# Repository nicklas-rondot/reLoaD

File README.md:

# *reLoaD* framework

The *reLoaD* (reconfigurable Lab on a Disc) framework is an open-hardware centrifugal microfluidics framework for research, teaching and application. It consists of three core modules:

1. The *Motor* module:
  Consists of a consumer-grade brushless DC (BLDC) motor driven by a PCB with a microcontroller, three-phase half bridge and magnetic encoder using field-oriented-control (FOC). This enables both high-speed rotation for centrifugal microfluidic operations and precise angular positioning for sensor alignment.
2. The *Base* module:
  A stationary PCB with a microcontroller that serves as a platform to mount/control stationary sensors and actuators. Furthermore, it integrates wireless power transmission electronics.
3. The *Spinnner* module:
  A PCB co-rotating with the microfluidic disc with a microcontroller that serves as a platform to mount/control co-rotating sensors and actuators (primarily heaters). It integrates rectification and power regulation electronics for wirelessly receiving power from the *Base* module.

All modules are based on the ESP32-S3 microcontroller. Sensors and actuators can be placed on *Shields*, PCBs that mount to the Base and Spinner modules using standard pin headers. It is advantageous to place optical sensors and actuators on a *Base Shield*, as this allows using the rotation of the microfluidic disc to align multiple chambers with a single sensor one after another. Moreover, it is recommended to place sensors and actuators that need to be in direct contact with the microfluidic disc on the *Spinner Shield*, since this enables interaction with the disc during rotation and necessitates no movable components. The control software is available at github.com/nicklas-rondot/reLoaD-control

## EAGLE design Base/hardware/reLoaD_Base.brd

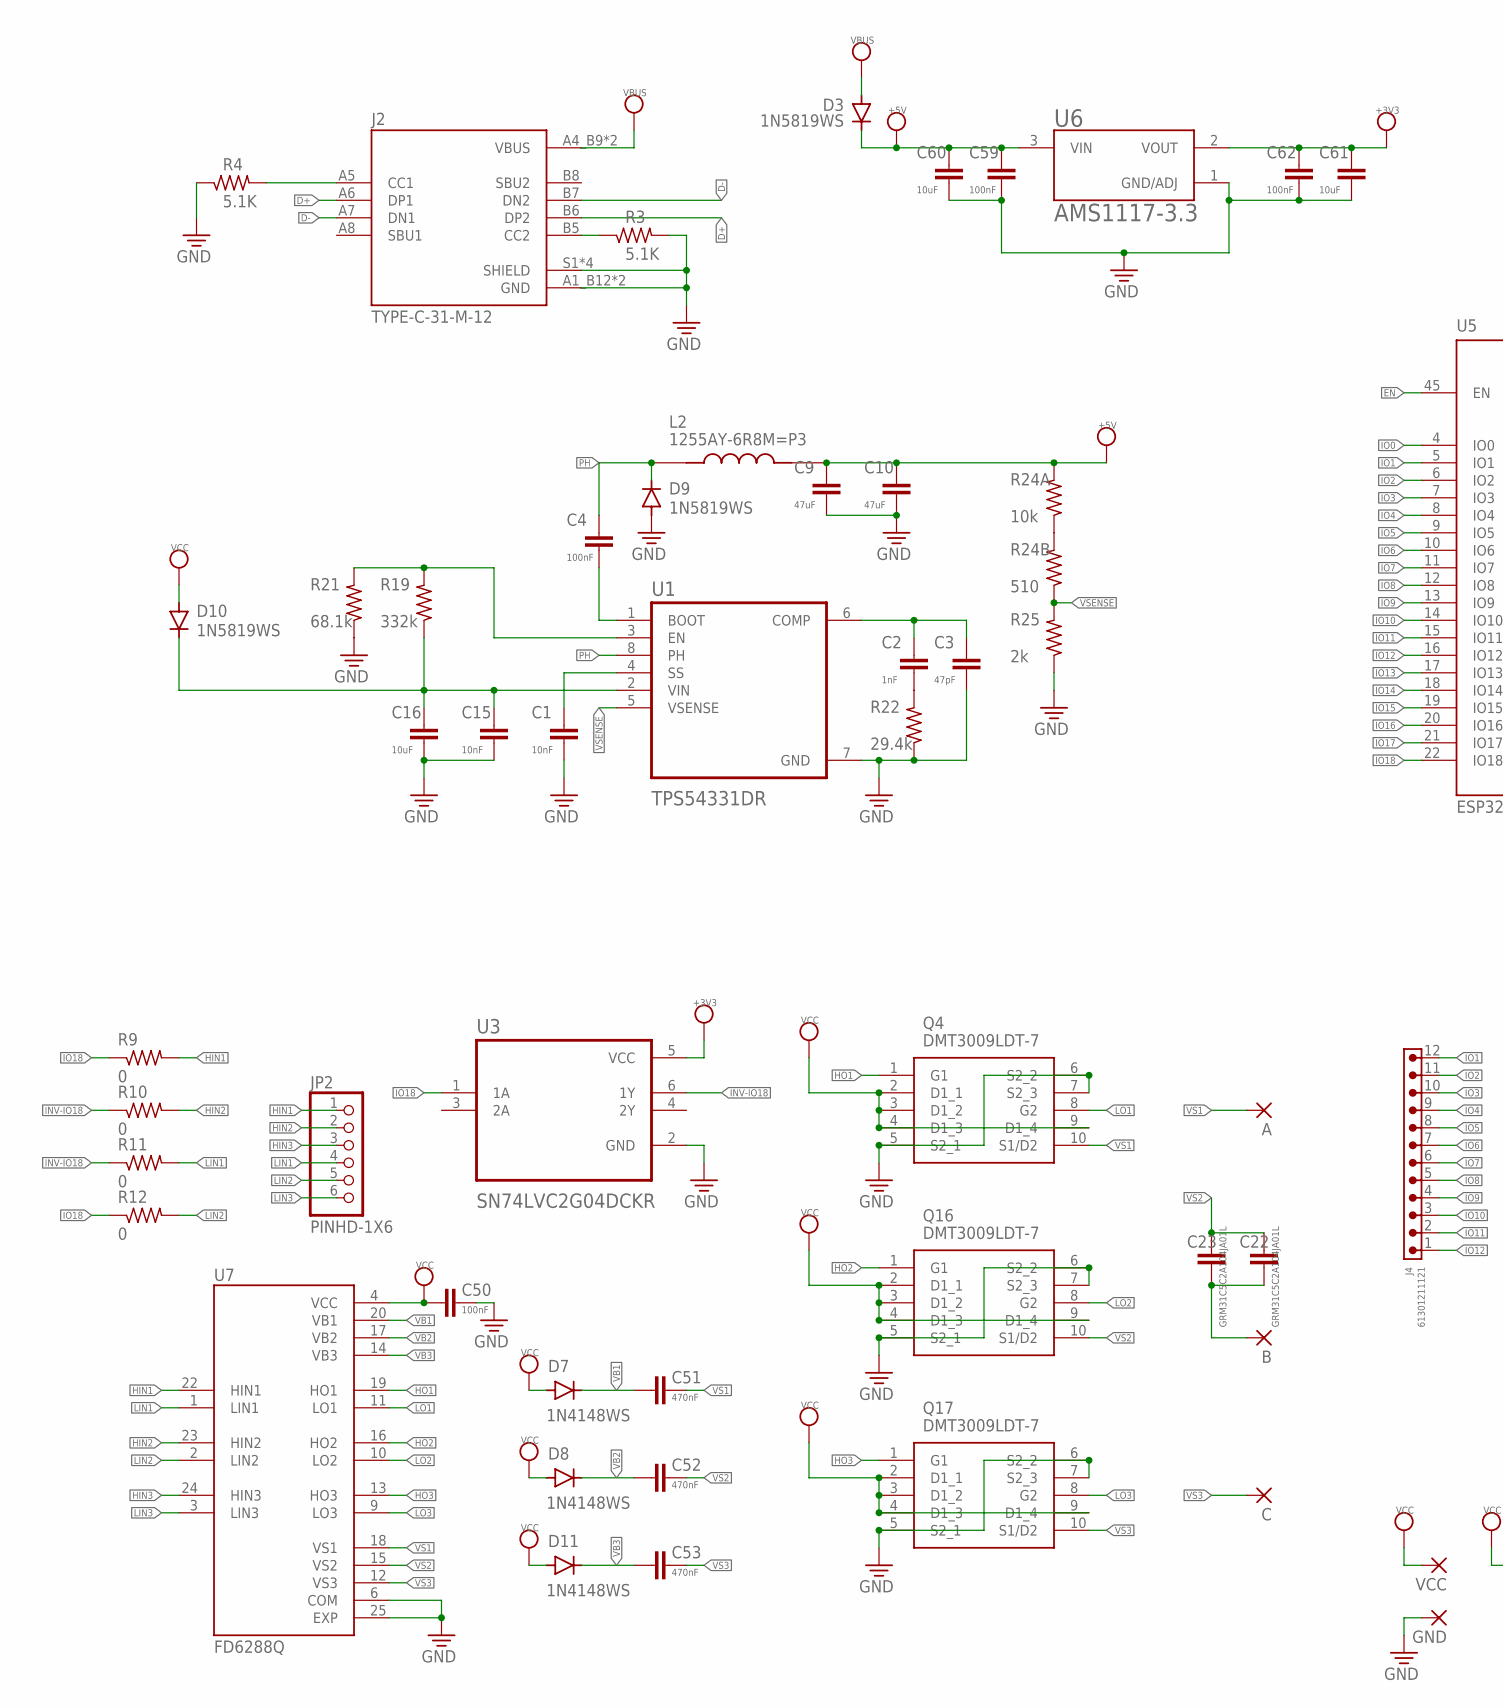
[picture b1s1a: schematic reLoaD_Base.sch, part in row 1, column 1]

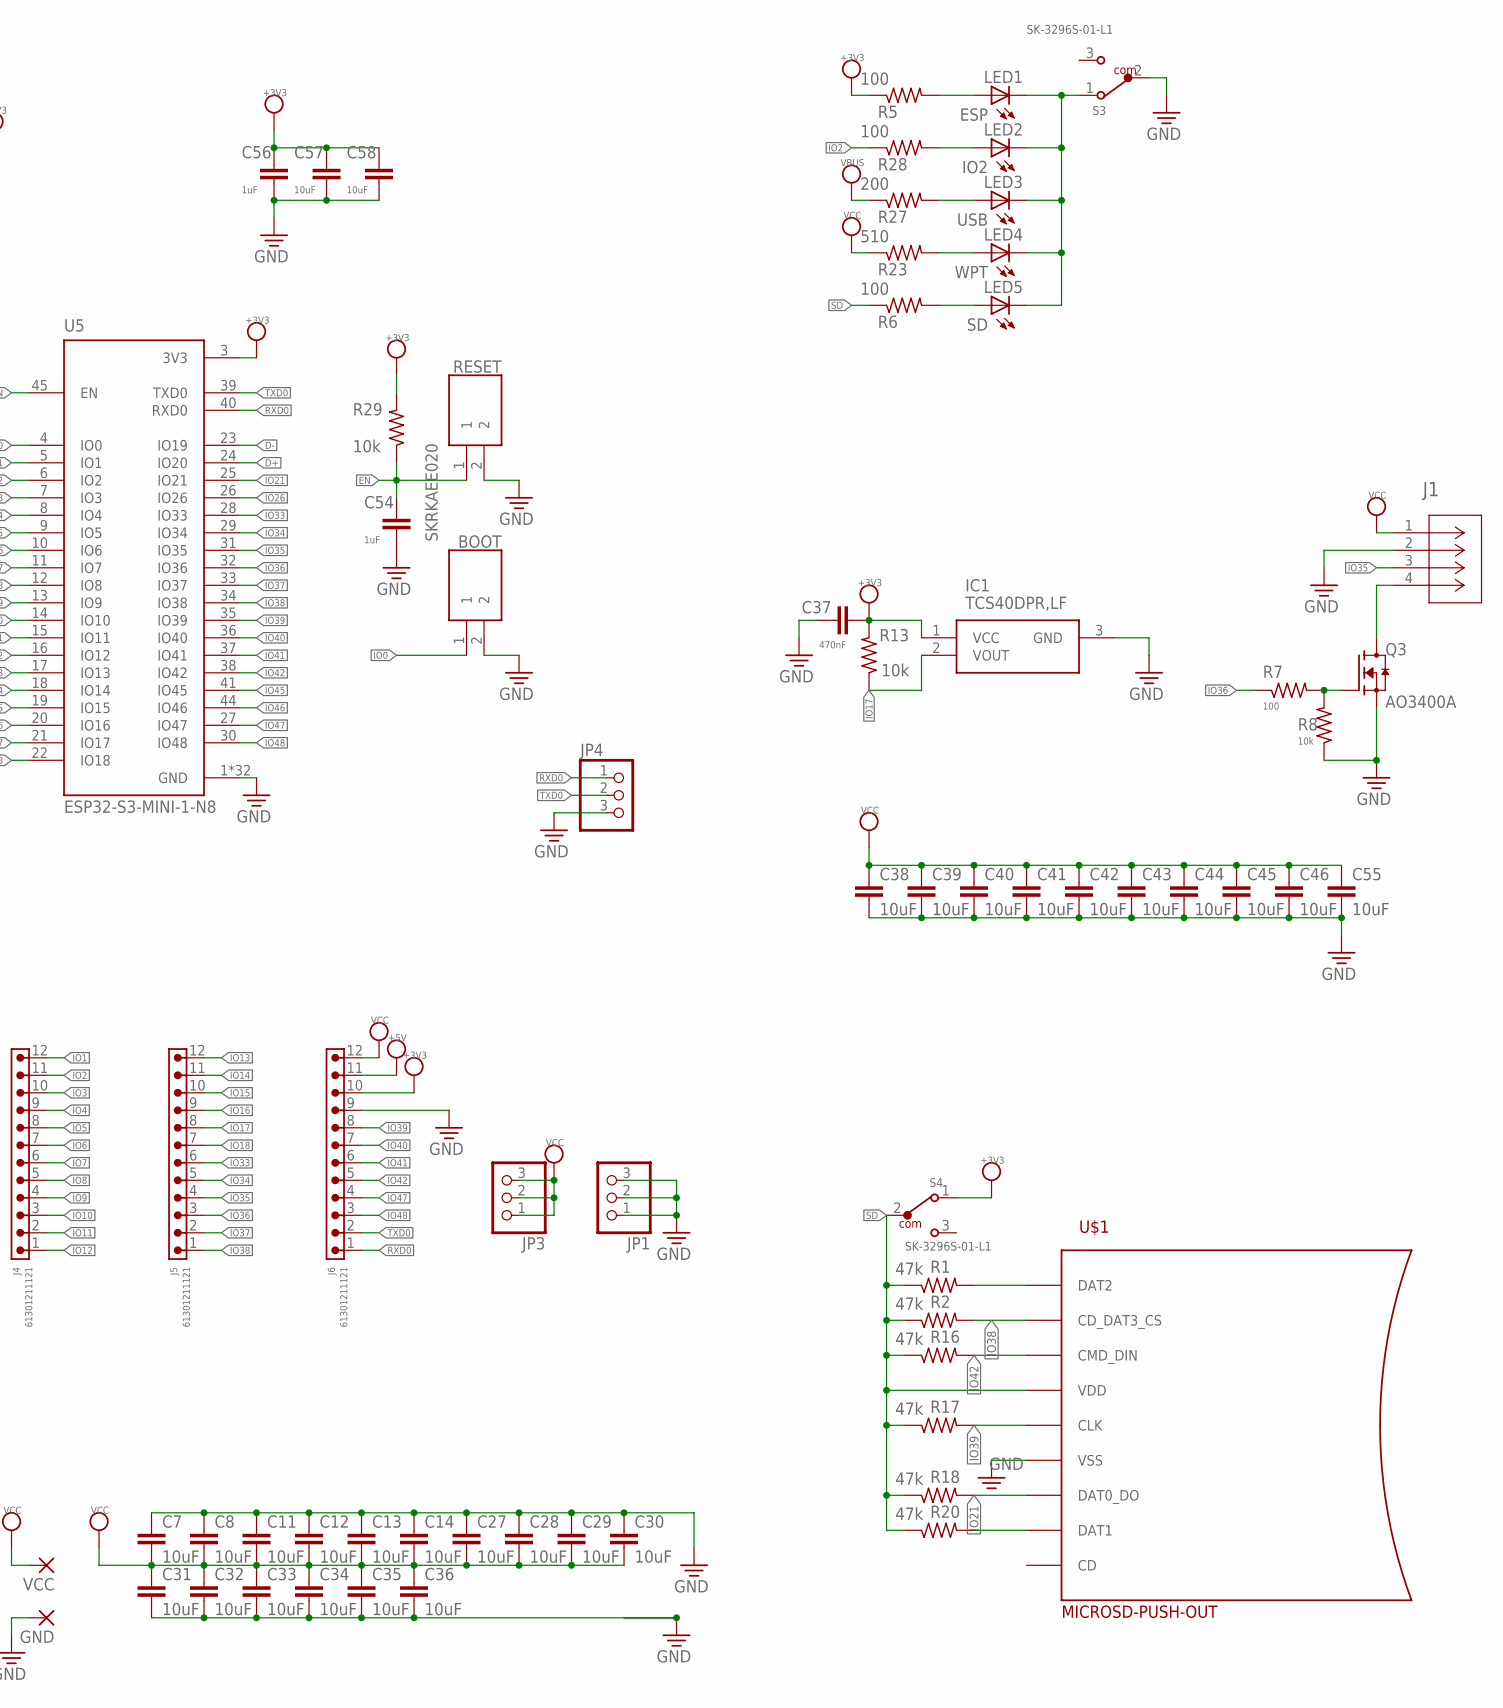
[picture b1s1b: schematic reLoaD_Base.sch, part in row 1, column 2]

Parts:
A: 3,81/1,4
B: 3,81/1,4
BOOT: SKRKAEE020
C: 3,81/1,4
C1, C15: 10nF; C0603K
C2: 1nF; C0603K
C3: 47pF; C0603K
C4, C50, C59, C62: 100nF; C0603K
C7, C8, C11, C12, C13, C14, C27, C28, C29, C30, C31, C32, C33, C34, C35, C36, C38, C39, C40, C41, C42, C43, C44, C45, C46, C55: 10uF; C0805K
C9, C10: 47uF; C0603K
C16, C57, C58, C60, C61: 10uF; C0603K
C22, C23: GRM31C5C2A104JA01L; C1206K
C37, C51, C52, C53: 470nF; C0603K
C54, C56: 1uF; C0603K
D3, D9, D10: 1N5819WS; SOD323-W
D7, D8, D11: 1N4148WS; SOD-323
GND: 3,81/1,4
IC1: TCS40DPR,LF; SOTFL95P240X88-3N
J1: S4B-XH-SM4-TBCONN4_S4B-XH_JST; CONN4_S4B-XH_JST
J2: TYPE-C-31-M-12; HRO_TYPE-C-31-M-12
J4, J5, J6: 61301211121
JP1, JP3, JP4: PINHD-1X3; 1X03
JP2: PINHD-1X6; 1X06
L2: 1255AY-6R8M=P3; IND_1255AY-6R8M=P3
LED1: ESP; CHIPLED_0805
LED2: IO2; CHIPLED_0805
LED3: USB; CHIPLED_0805
LED4: WPT; CHIPLED_0805
LED5: SD; CHIPLED_0805
Q3: AO3400A; SOT95P280X125-3N
Q4, Q16, Q17: DMT3009LDT-7; DMT3009LDT7
R1, R2, R16, R17, R18, R20: 47k; R0603
R3, R4: 5.1K; R0603
R5, R6, R7, R28: 100; R0603
R8, R13, R24A, R29: 10k; R0603
R9, R10, R11, R12: 0; R0603
R19: 332k; R0603
R21: 68.1k; R0603
R22: 29.4k; R0603
R23, R24B: 510; R0603
R25: 2k; R0603
R27: 200; R0603
RESET: SKRKAEE020
S3, S4: SK-3296S-01-L1; 450404015514
U1: TPS54331DR; SOIC127P599X175-8N
U3: SN74LVC2G04DCKR; SOT65P210X110-6N
U5: ESP32-S3-MINI-1-N8; XCVR_ESP32-S3-MINI-1-N8
U6: AMS1117-3.3; SOT229P700X180-4N
U7: FD6288Q; QFN50P400X400X90-25N
U$1: MICROSD-PUSH-OUT
VCC: 3,81/1,4

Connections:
+3V3: C37.2, C56.1, C57.1, C58.1, C61.1, C62.1, IC1.1 (VCC), J6.10, R5.1, R13.2, R29.2, S4.1, U3.5 (VCC), U5.3 (3V3), U6.2 (VOUT)
+5V: C9.1, C10.1, C59.1, C60.1, D3.C, J6.11, L2.2, R24A.2, U6.3 (VIN)
COIL2R1: B.1, C22.1, C23.1
D+: J2.A6 (DP1), J2.B6 (DP2), U5.24 (IO20)
D-: J2.A7 (DN1), J2.B7 (DN2), U5.23 (IO19)
DAT2: R1.2, U$1.1 (DAT2)
EN: C54.1, R29.1, RESET.1, U5.45 (EN)
GND: BOOT.2, C1.2, C3.2, C7.1, C8.1, C9.2, C10.2, C11.1, C12.1, C13.1, C14.1, C15.2, C16.2, C27.1, C28.1, C29.1, C30.1, C31.2, C32.2, C33.2, C34.2, C35.2, C36.2, C37.1, C38.2, C39.2, C40.2, C41.2, C42.2, C43.2, C44.2, C45.2, C46.2, C50.1, C54.2, C55.2, C56.2, C57.2, C58.2, C59.2, C60.2, C61.2, C62.2, D9.A, GND.1, IC1.3 (GND), J1.2, J2.A1_B12 (GND), J2.B1_A12 (GND), J2.S1 (SHIELD), J2.S2 (SHIELD), J2.S3 (SHIELD), J2.S4 (SHIELD), J6.9, JP1.1, JP1.2, JP1.3, JP4.3, Q3.2 (S), Q4.5 (S2_1), Q4.6 (S2_2), Q4.7 (S2_3), Q16.5 (S2_1), Q16.6 (S2_2), Q16.7 (S2_3), Q17.5 (S2_1), Q17.6 (S2_2), Q17.7 (S2_3), R3.2, R4.1, R8.1, R21.1, R22.1, R25.1, RESET.2, S3.2, U1.7 (GND), U3.2 (GND), U5.1 (GND), U5.2 (GND), U5.42 (GND), U5.43 (GND), U5.46 (GND), U5.47 (GND), U5.48 (GND), U5.49 (GND), U5.50 (GND), U5.51 (GND), U5.52 (GND), U5.53 (GND), U5.54 (GND), U5.55 (GND), U5.56 (GND), U5.57 (GND), U5.58 (GND), U5.59 (GND), U5.60 (GND), U5.61 (GND), U5.61_1 (GND), U5.61_2 (GND), U5.61_3 (GND), U5.61_4 (GND), U5.61_5 (GND), U5.61_6 (GND), U5.61_7 (GND), U5.61_8 (GND), U5.62 (GND), U5.63 (GND), U5.64 (GND), U5.65 (GND), U6.1 (GND/ADJ), U7.6 (COM), U7.25 (EXP), U$1.6 (VSS), U$1.G1 (VSS), U$1.G2 (VSS), U$1.G3 (VSS), U$1.G4 (VSS)
HIN1: JP2.1, R9.2, U7.22 (HIN1)
HIN2: JP2.2, R10.2, U7.23 (HIN2)
HIN3: JP2.3, U7.24 (HIN3)
HO1: Q4.1 (G1), U7.19 (HO1)
HO2: Q16.1 (G1), U7.16 (HO2)
HO3: Q17.1 (G1), U7.13 (HO3)
INV-IO18: R10.1, R11.1, U3.6 (1Y)
IO0: BOOT.1, U5.4 (IO0)
IO1: J4.12, U5.5 (IO1)
IO2: J4.11, R28.1, U5.6 (IO2)
IO3: J4.10, U5.7 (IO3)
IO4: J4.9, U5.8 (IO4)
IO5: J4.8, U5.9 (IO5)
IO6: J4.7, U5.10 (IO6)
IO7: J4.6, U5.11 (IO7)
IO8: J4.5, U5.12 (IO8)
IO9: J4.4, U5.13 (IO9)
IO10: J4.3, U5.14 (IO10)
IO11: J4.2, U5.15 (IO11)
IO12: J4.1, U5.16 (IO12)
IO13: J5.12, U5.17 (IO13)
IO14: J5.11, U5.18 (IO14)
IO15: J5.10, U5.19 (IO15)
IO16: J5.9, U5.20 (IO16)
IO17: IC1.2 (VOUT), J5.8, R13.1, U5.21 (IO17)
IO18: J5.7, R9.1, R12.1, U3.1 (1A), U5.22 (IO18)
IO21: R18.2, U5.25 (IO21), U$1.7 (DAT0_DO)
IO26: U5.26 (IO26)
IO33: J5.6, U5.28 (IO33)
IO34: J5.5, U5.29 (IO34)
IO35: J1.3, J5.4, U5.31 (IO35)
IO36: J5.3, R7.1, U5.32 (IO36)
IO37: J5.2, U5.33 (IO37)
IO38: J5.1, R2.2, U5.34 (IO38), U$1.2 (CD_DAT3_CS)
IO39: J6.8, R17.2, U5.35 (IO39), U$1.5 (CLK)
IO40: J6.7, U5.36 (IO40)
IO41: J6.6, U5.37 (IO41)
IO42: J6.5, R16.2, U5.38 (IO42), U$1.3 (CMD_DIN)
IO45: U5.41 (IO45)
IO46: U5.44 (IO46)
IO47: J6.4, U5.27 (IO47)
IO48: J6.3, U5.30 (IO48)
LIN1: JP2.4, R11.2, U7.1 (LIN1)
LIN2: JP2.5, R12.2, U7.2 (LIN2)
LIN3: JP2.6, U7.3 (LIN3)
LO1: Q4.8 (G2), U7.11 (LO1)
LO2: Q16.8 (G2), U7.10 (LO2)
LO3: Q17.8 (G2), U7.9 (LO3)
unnamed: LED3.A, R27.2
unnamed: LED4.A, R23.2
unnamed: J1.4, Q3.3 (D)
unnamed: J2.B5 (CC2), R3.1
unnamed: LED1.C, LED2.C, LED3.C, LED4.C, LED5.C, S3.1
unnamed: LED2.A, R28.2
unnamed: R19.2, R21.2, U1.3 (EN)
unnamed: C1.1, U1.4 (SS)
unnamed: R20.2, U$1.8 (DAT1)
unnamed: C2.1, C3.1, U1.6 (COMP)
unnamed: C2.2, R22.2
unnamed: Q3.1 (G), R7.2, R8.2
unnamed: LED1.A, R5.2
unnamed: LED5.A, R6.2
unnamed: R24A.1, R24B.2
unnamed: C4.2, U1.1 (BOOT)
unnamed: C15.1, C16.1, D10.C, R19.1, U1.2 (VIN)
unnamed: J2.A5 (CC1), R4.2
PH: C4.1, D9.C, L2.1, U1.8 (PH)
RXD0: J6.1, JP4.1, U5.40 (RXD0)
SD: R1.1, R2.1, R6.1, R16.1, R17.1, R18.1, R20.1, S4.2, U$1.4 (VDD)
TXD0: J6.2, JP4.2, U5.39 (TXD0)
VB1: C51.1, D7.C, U7.20 (VB1)
VB2: C52.1, D8.C, U7.17 (VB2)
VB3: C53.1, D11.C, U7.14 (VB3)
VBUS: D3.A, J2.A4_B9 (VBUS), J2.B4_A9 (VBUS), R27.1
VCC: C7.2, C8.2, C11.2, C12.2, C13.2, C14.2, C27.2, C28.2, C29.2, C30.2, C31.1, C32.1, C33.1, C34.1, C35.1, C36.1, C38.1, C39.1, C40.1, C41.1, C42.1, C43.1, C44.1, C45.1, C46.1, C50.2, C55.1, D7.A, D8.A, D10.A, D11.A, J1.1, J6.12, JP3.1, JP3.2, JP3.3, Q4.2 (D1_1), Q4.3 (D1_2), Q4.4 (D1_3), Q4.9 (D1_4), Q16.2 (D1_1), Q16.3 (D1_2), Q16.4 (D1_3), Q16.9 (D1_4), Q17.2 (D1_1), Q17.3 (D1_2), Q17.4 (D1_3), Q17.9 (D1_4), R23.1, U7.4 (VCC), VCC.1
VS1: A.1, C51.2, Q4.10 (S1/D2), U7.18 (VS1)
VS2: C22.2, C23.2, C52.2, Q16.10 (S1/D2), U7.15 (VS2)
VS3: C.1, C53.2, Q17.10 (S1/D2), U7.12 (VS3)
VSENSE: R24B.1, R25.2, U1.5 (VSENSE)

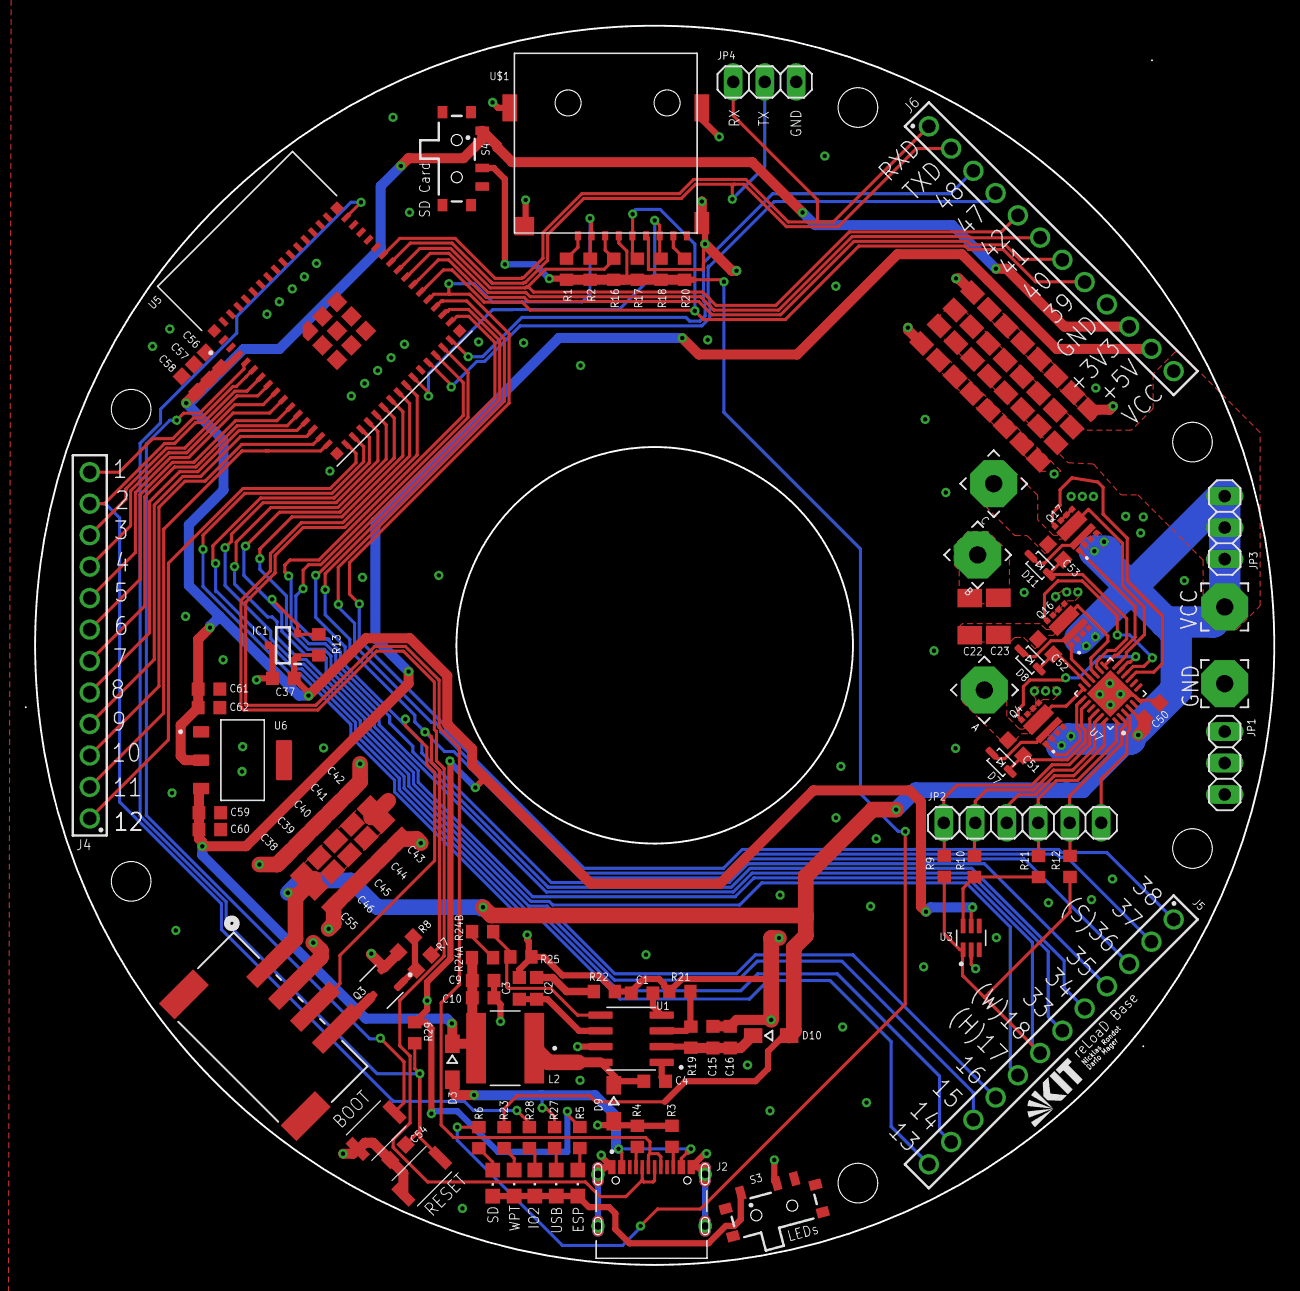
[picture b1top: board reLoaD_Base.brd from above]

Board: 2 copper layers, 100.8 x 100.0 mm, 117 parts (0 on the bottom side), 84 nets.

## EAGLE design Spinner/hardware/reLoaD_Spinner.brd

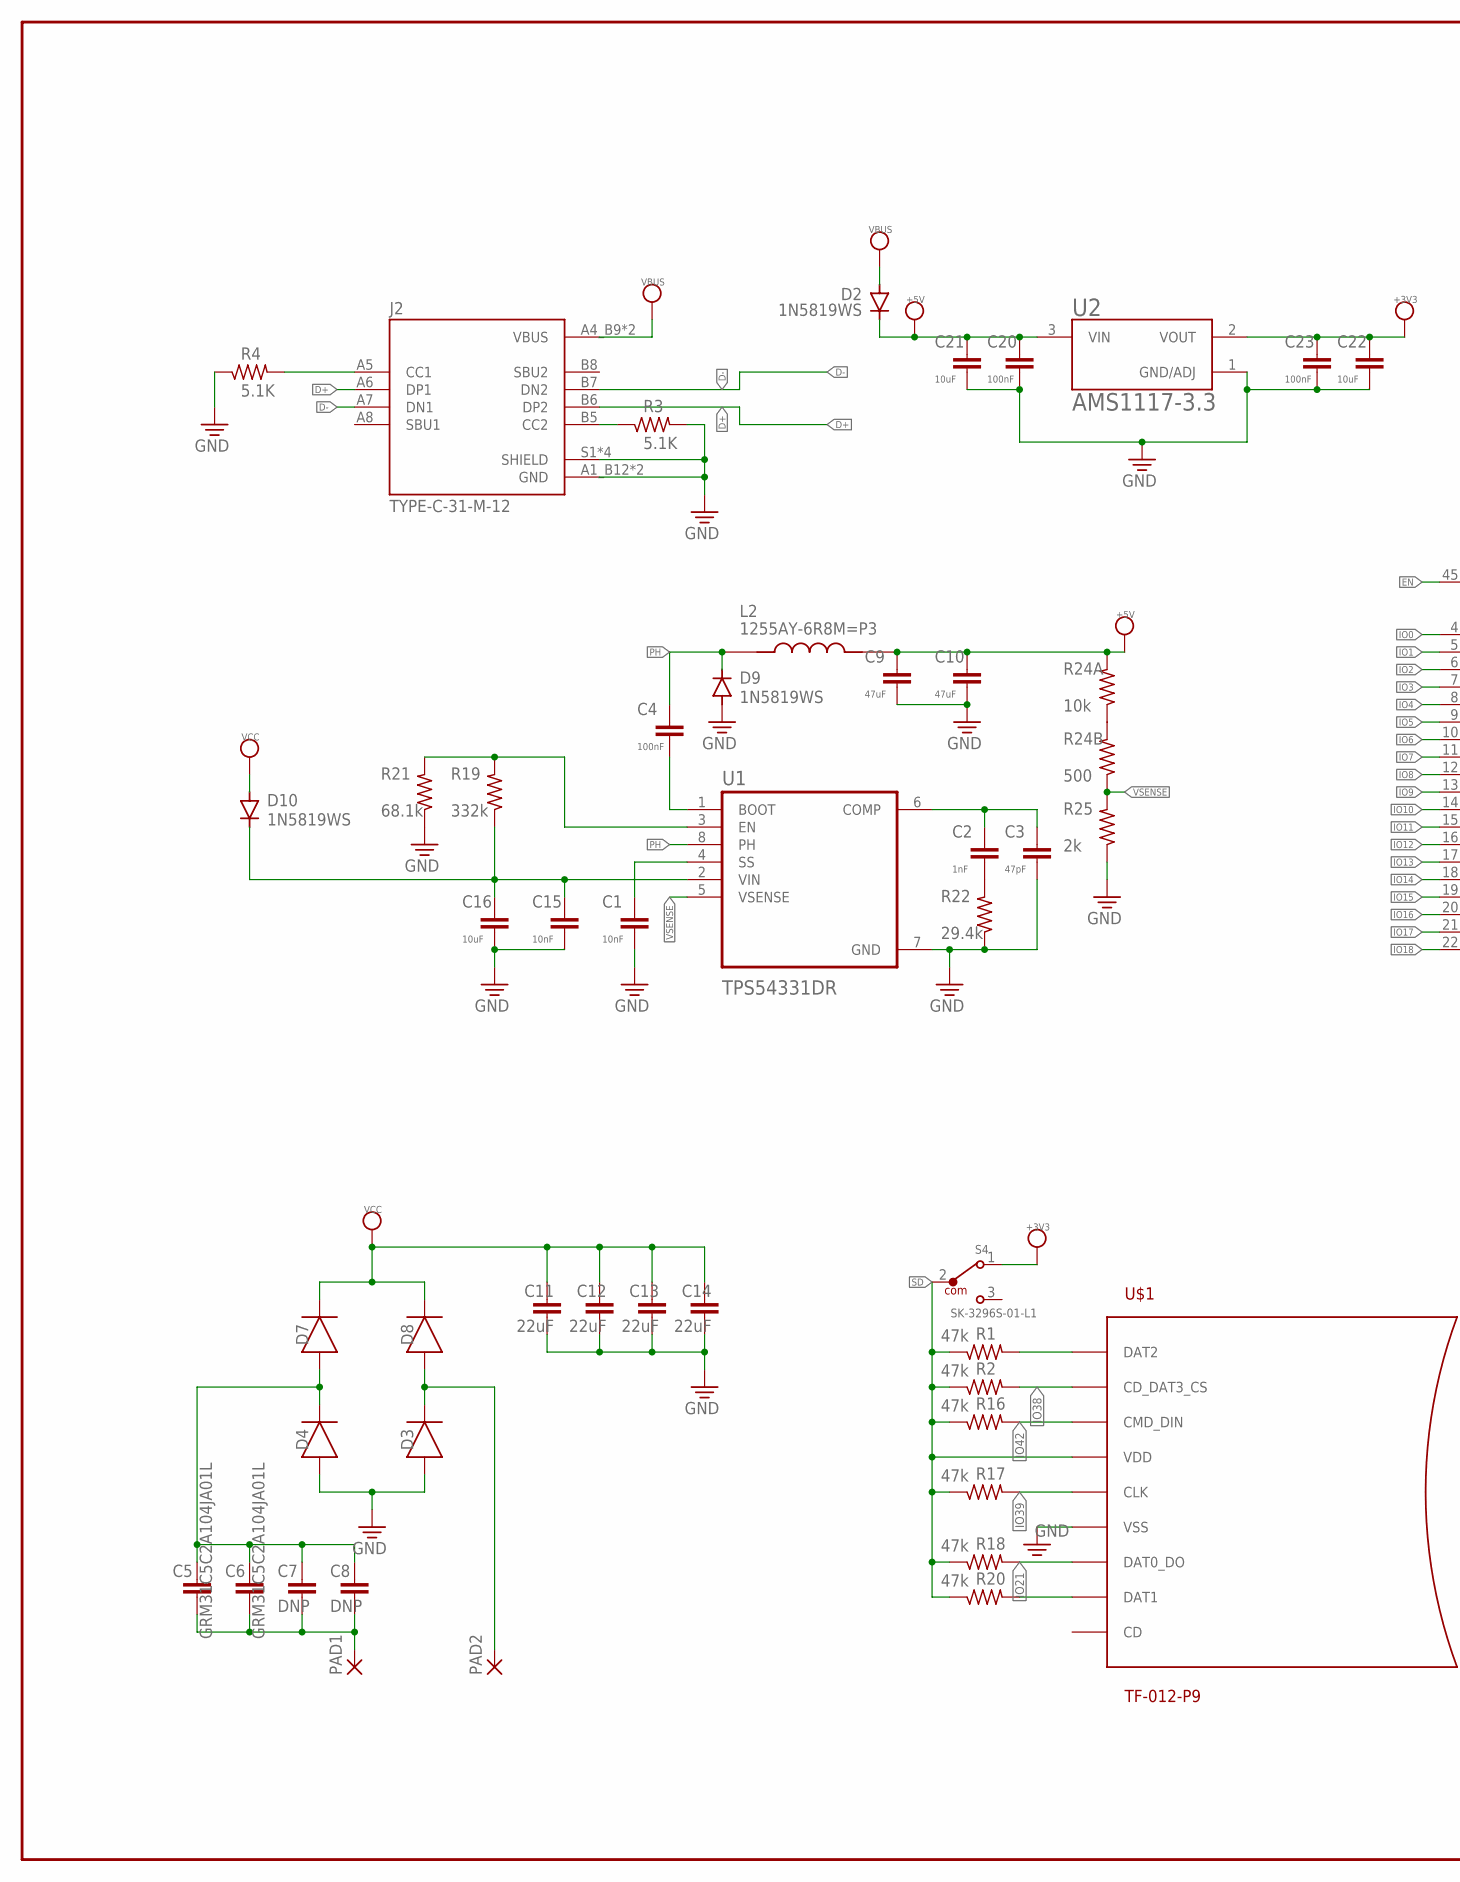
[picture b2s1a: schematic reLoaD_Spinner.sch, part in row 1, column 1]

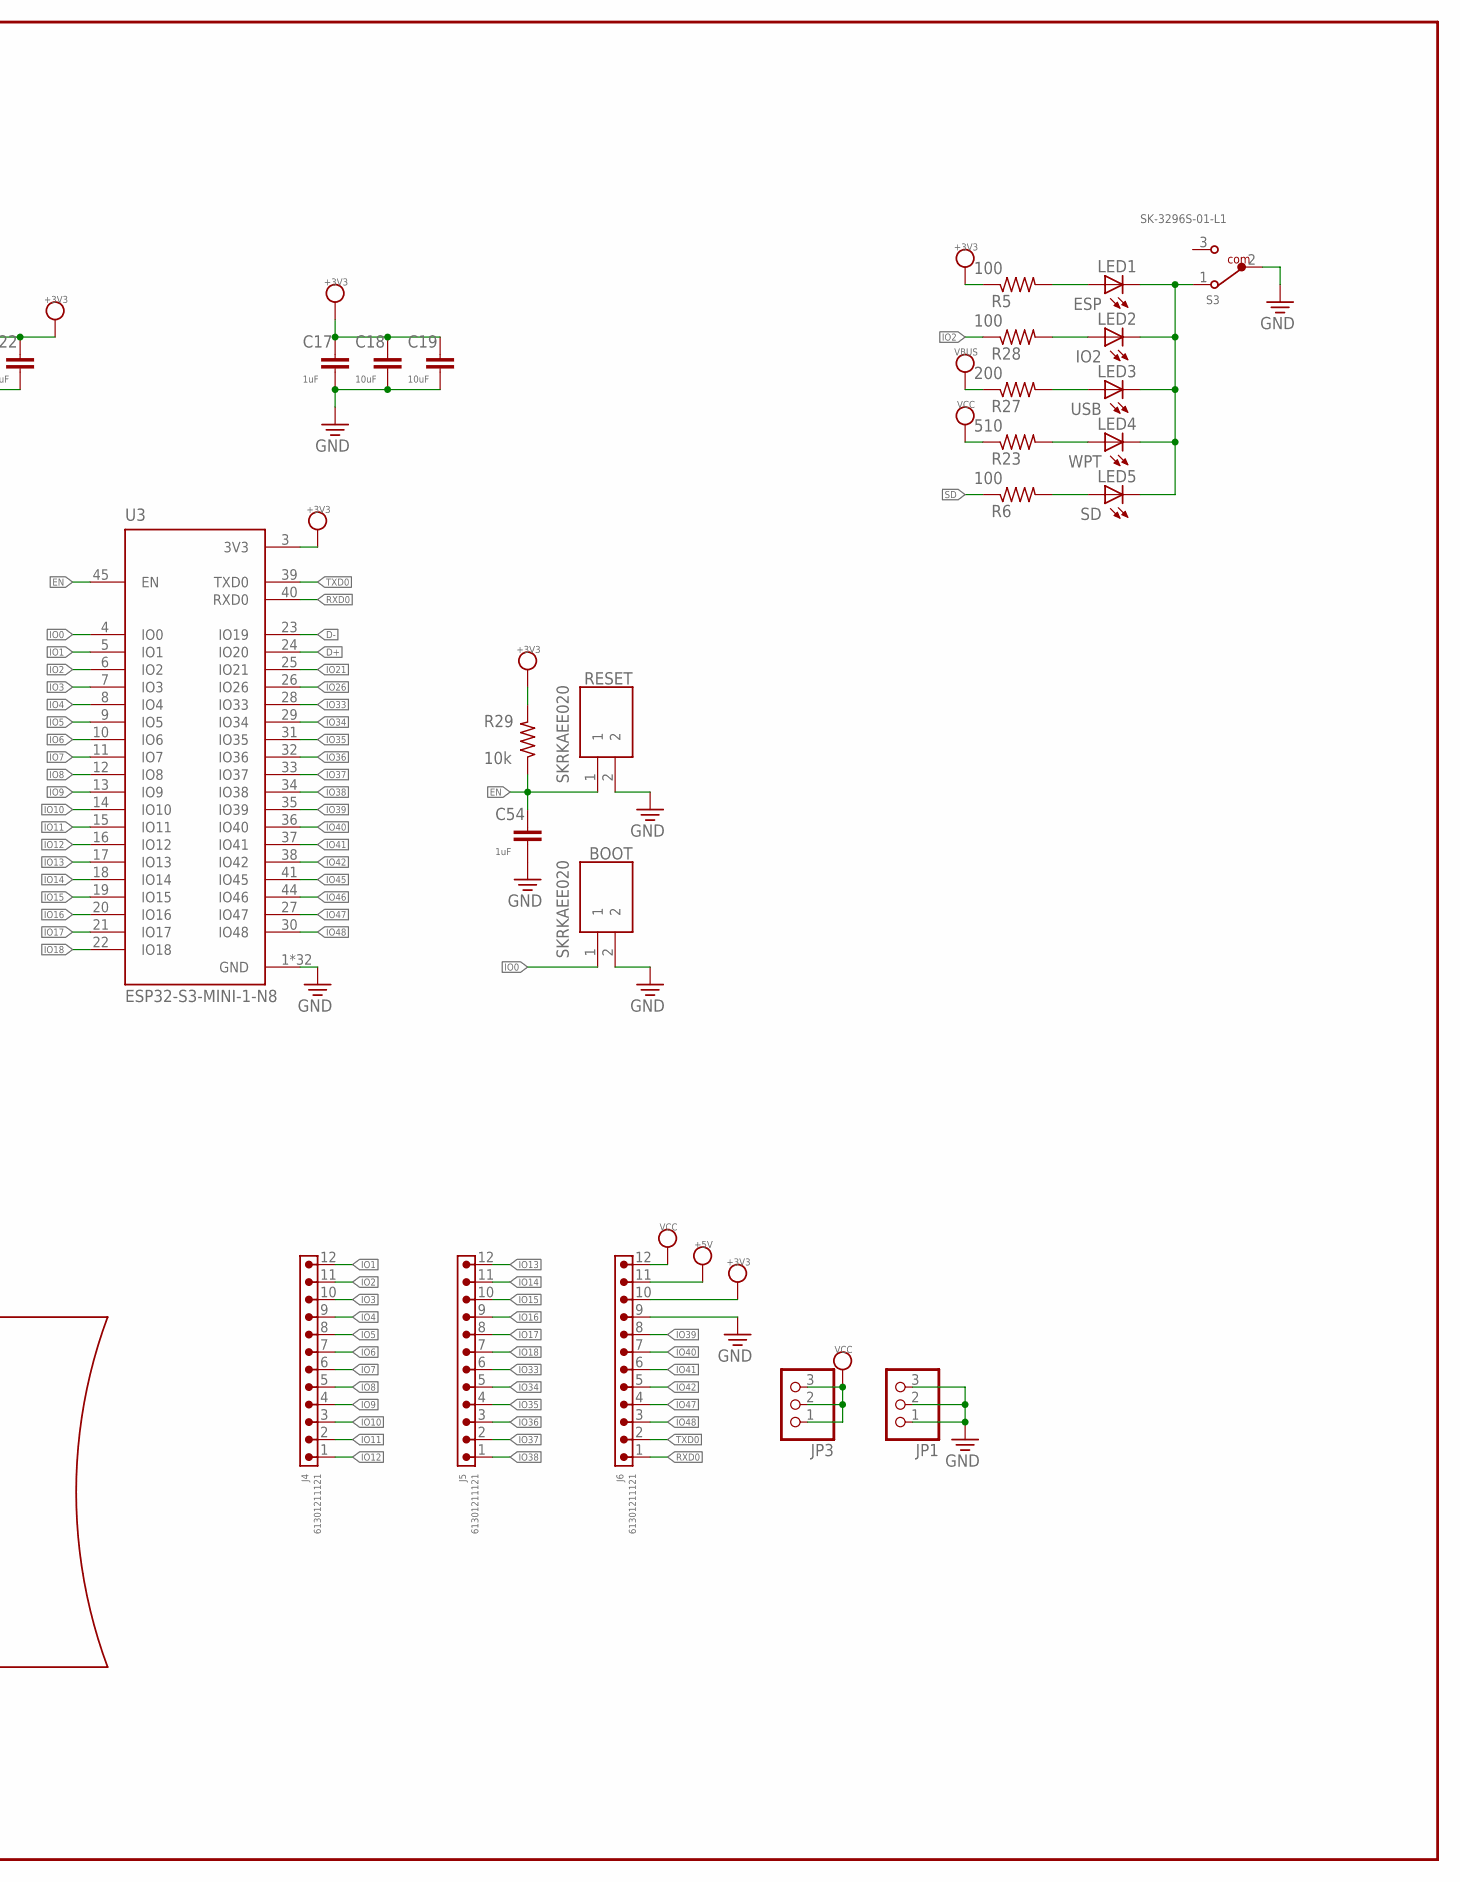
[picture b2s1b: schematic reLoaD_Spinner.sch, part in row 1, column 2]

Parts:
BOOT: SKRKAEE020
C1, C15: 10nF; C0603K
C2: 1nF; C0603K
C3: 47pF; C0603K
C4, C20, C23: 100nF; C0603K
C5, C6: GRM31C5C2A104JA01L; C1206K
C7, C8: DNP; C1206K
C9, C10: 47uF; C0603K
C11, C12, C13, C14: 22uF; C0805K
C16, C18, C19, C21, C22: 10uF; C0603K
C17, C54: 1uF; C0603K
D2, D9, D10: 1N5819WS; SOD323-W
D3, D4, D7, D8: DIODE; DIOM5226X290N
J2: TYPE-C-31-M-12; HRO_TYPE-C-31-M-12
J4, J5, J6: 61301211121
JP1, JP3: PINHD-1X3; 1X03
L2: 1255AY-6R8M=P3; IND_1255AY-6R8M=P3
LED1: ESP; CHIPLED_0805
LED2: IO2; CHIPLED_0805
LED3: USB; CHIPLED_0805
LED4: WPT; CHIPLED_0805
LED5: SD; CHIPLED_0805
PAD1, PAD2: 3,81/1,4
R1, R2, R16, R17, R18, R20: 47k; R0603
R3, R4: 5.1K; R0603
R5, R6, R28: 100; R0603
R19: 332k; R0603
R21: 68.1k; R0603
R22: 29.4k; R0603
R23: 510; R0603
R24A, R29: 10k; R0603
R24B: 500; R0603
R25: 2k; R0603
R27: 200; R0603
RESET: SKRKAEE020
S3, S4: SK-3296S-01-L1; 450404015514
U1: TPS54331DR; SOIC127P599X175-8N
U2: AMS1117-3.3; SOT229P700X180-4N
U3: ESP32-S3-MINI-1-N8; XCVR_ESP32-S3-MINI-1-N8
U$1: TF-012-P9; MICROSD-PUSH-OUT

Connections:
+3V3: C17.1, C18.1, C19.1, C22.1, C23.1, J6.10, R5.1, R29.2, S4.1, U2.2 (VOUT), U3.3 (3V3)
+5V: C9.1, C10.1, C20.1, C21.1, D2.C, J6.11, L2.2, R24A.2, U2.3 (VIN)
COIL1: C5.2, C6.2, C7.2, C8.2, PAD1.1
COIL2: D3.1 (C), D8.2 (A), PAD2.1
D+: J2.A6 (DP1), J2.B6 (DP2), U3.24 (IO20)
D-: J2.A7 (DN1), J2.B7 (DN2), U3.23 (IO19)
DAT2: R1.2, U$1.1 (DAT2)
EN: C54.1, R29.1, RESET.1, U3.45 (EN)
GND: BOOT.2, C1.2, C3.2, C9.2, C10.2, C11.1, C12.1, C13.1, C14.1, C15.2, C16.2, C17.2, C18.2, C19.2, C20.2, C21.2, C22.2, C23.2, C54.2, D3.2 (A), D4.2 (A), D9.A, J2.A1_B12 (GND), J2.B1_A12 (GND), J2.S1 (SHIELD), J2.S2 (SHIELD), J2.S3 (SHIELD), J2.S4 (SHIELD), J6.9, JP1.1, JP1.2, JP1.3, R3.2, R4.1, R21.1, R22.1, R25.1, RESET.2, S3.2, U1.7 (GND), U2.1 (GND/ADJ), U3.1 (GND), U3.2 (GND), U3.42 (GND), U3.43 (GND), U3.46 (GND), U3.47 (GND), U3.48 (GND), U3.49 (GND), U3.50 (GND), U3.51 (GND), U3.52 (GND), U3.53 (GND), U3.54 (GND), U3.55 (GND), U3.56 (GND), U3.57 (GND), U3.58 (GND), U3.59 (GND), U3.60 (GND), U3.61 (GND), U3.61_1 (GND), U3.61_2 (GND), U3.61_3 (GND), U3.61_4 (GND), U3.61_5 (GND), U3.61_6 (GND), U3.61_7 (GND), U3.61_8 (GND), U3.62 (GND), U3.63 (GND), U3.64 (GND), U3.65 (GND), U$1.6 (VSS), U$1.G1 (VSS), U$1.G2 (VSS), U$1.G3 (VSS), U$1.G4 (VSS)
IO0: BOOT.1, U3.4 (IO0)
IO1: J4.12, U3.5 (IO1)
IO2: J4.11, R28.1, U3.6 (IO2)
IO3: J4.10, U3.7 (IO3)
IO4: J4.9, U3.8 (IO4)
IO5: J4.8, U3.9 (IO5)
IO6: J4.7, U3.10 (IO6)
IO7: J4.6, U3.11 (IO7)
IO8: J4.5, U3.12 (IO8)
IO9: J4.4, U3.13 (IO9)
IO10: J4.3, U3.14 (IO10)
IO11: J4.2, U3.15 (IO11)
IO12: J4.1, U3.16 (IO12)
IO13: J5.12, U3.17 (IO13)
IO14: J5.11, U3.18 (IO14)
IO15: J5.10, U3.19 (IO15)
IO16: J5.9, U3.20 (IO16)
IO17: J5.8, U3.21 (IO17)
IO18: J5.7, U3.22 (IO18)
IO21: R18.2, U3.25 (IO21), U$1.7 (DAT0_DO)
IO26: U3.26 (IO26)
IO33: J5.6, U3.28 (IO33)
IO34: J5.5, U3.29 (IO34)
IO35: J5.4, U3.31 (IO35)
IO36: J5.3, U3.32 (IO36)
IO37: J5.2, U3.33 (IO37)
IO38: J5.1, R2.2, U3.34 (IO38), U$1.2 (CD_DAT3_CS)
IO39: J6.8, R17.2, U3.35 (IO39), U$1.5 (CLK)
IO40: J6.7, U3.36 (IO40)
IO41: J6.6, U3.37 (IO41)
IO42: J6.5, R16.2, U3.38 (IO42), U$1.3 (CMD_DIN)
IO45: U3.41 (IO45)
IO46: U3.44 (IO46)
IO47: J6.4, U3.27 (IO47)
IO48: J6.3, U3.30 (IO48)
unnamed: LED3.A, R27.2
unnamed: LED4.A, R23.2
unnamed: J2.B5 (CC2), R3.1
unnamed: LED1.C, LED2.C, LED3.C, LED4.C, LED5.C, S3.1
unnamed: LED2.A, R28.2
unnamed: R19.2, R21.2, U1.3 (EN)
unnamed: C1.1, U1.4 (SS)
unnamed: R20.2, U$1.8 (DAT1)
unnamed: C2.1, C3.1, U1.6 (COMP)
unnamed: C2.2, R22.2
unnamed: LED5.A, R6.2
unnamed: LED1.A, R5.2
unnamed: R24A.1, R24B.2
unnamed: C5.1, C6.1, C7.1, C8.1, D4.1 (C), D7.2 (A)
unnamed: C4.2, U1.1 (BOOT)
unnamed: C15.1, C16.1, D10.C, R19.1, U1.2 (VIN)
unnamed: J2.A5 (CC1), R4.2
PH: C4.1, D9.C, L2.1, U1.8 (PH)
RXD0: J6.1, U3.40 (RXD0)
SD: R1.1, R2.1, R6.1, R16.1, R17.1, R18.1, R20.1, S4.2, U$1.4 (VDD)
TXD0: J6.2, U3.39 (TXD0)
VBUS: D2.A, J2.A4_B9 (VBUS), J2.B4_A9 (VBUS), R27.1
VCC: C11.2, C12.2, C13.2, C14.2, D7.1 (C), D8.1 (C), D10.A, J6.12, JP3.1, JP3.2, JP3.3, R23.1
VSENSE: R24B.1, R25.2, U1.5 (VSENSE)

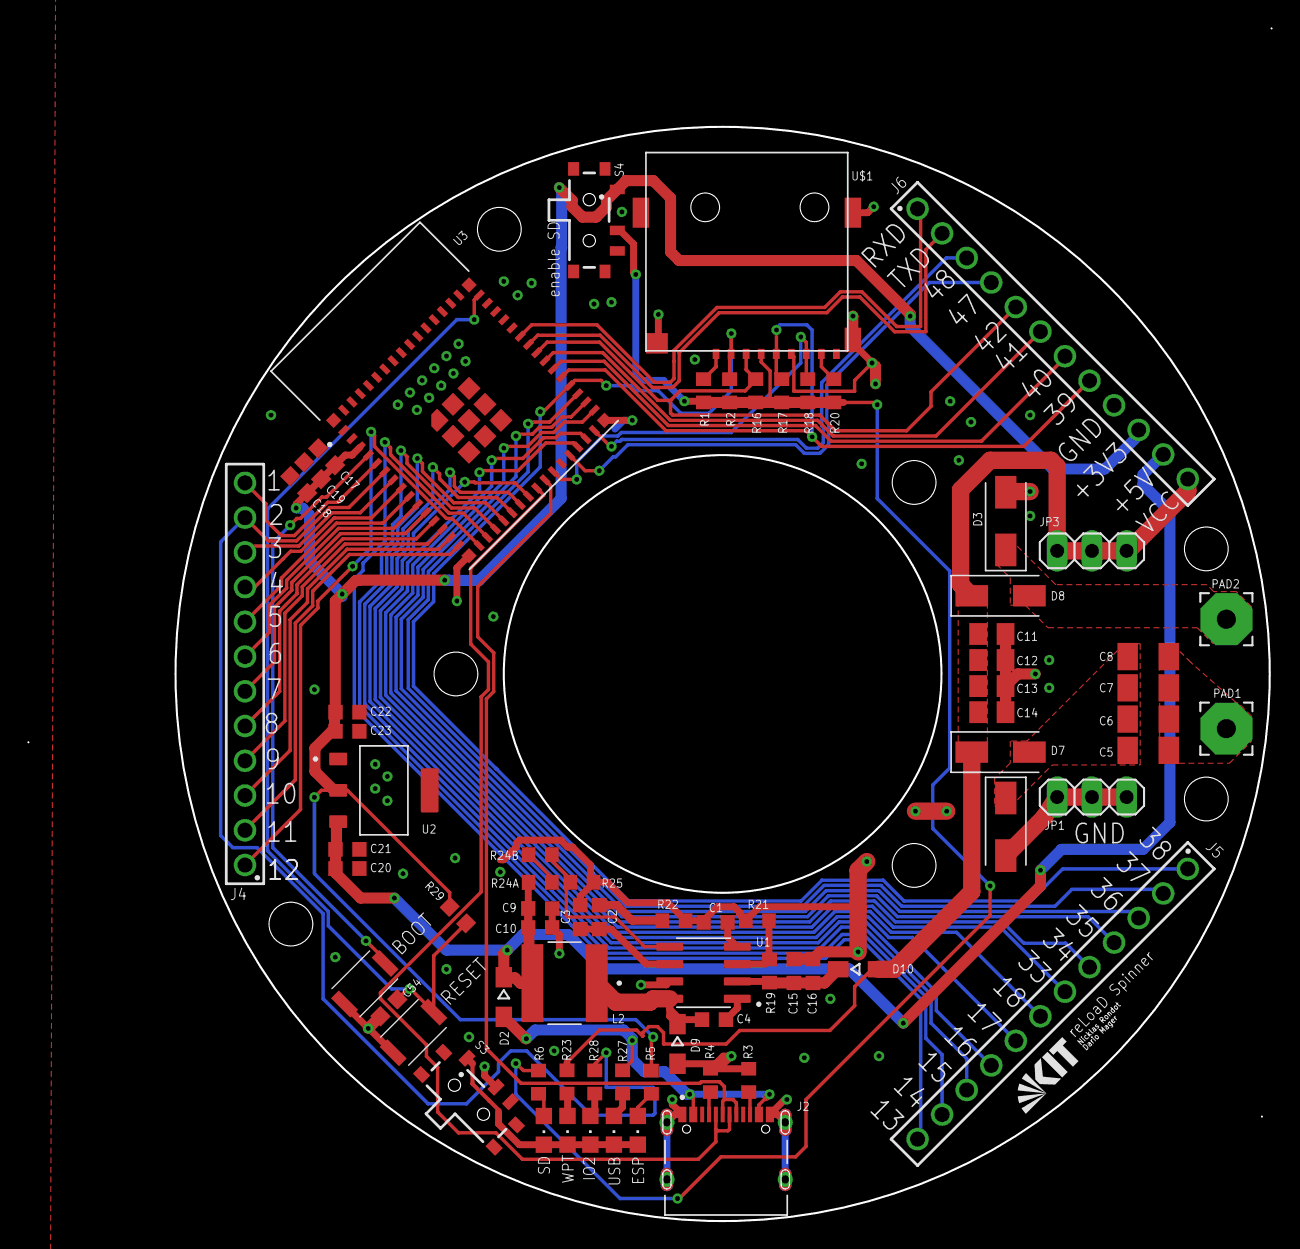
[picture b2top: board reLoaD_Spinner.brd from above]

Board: 2 copper layers, 80.0 x 80.0 mm, 73 parts (0 on the bottom side), 65 nets.

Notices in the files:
parts and their libraries:
Wurth_Connectors_WR-PHD: Copyright: Würth Elektronik
COPYRIGHT: Copyright (C) 2024 Ultra Librarian. All rights reserved.
